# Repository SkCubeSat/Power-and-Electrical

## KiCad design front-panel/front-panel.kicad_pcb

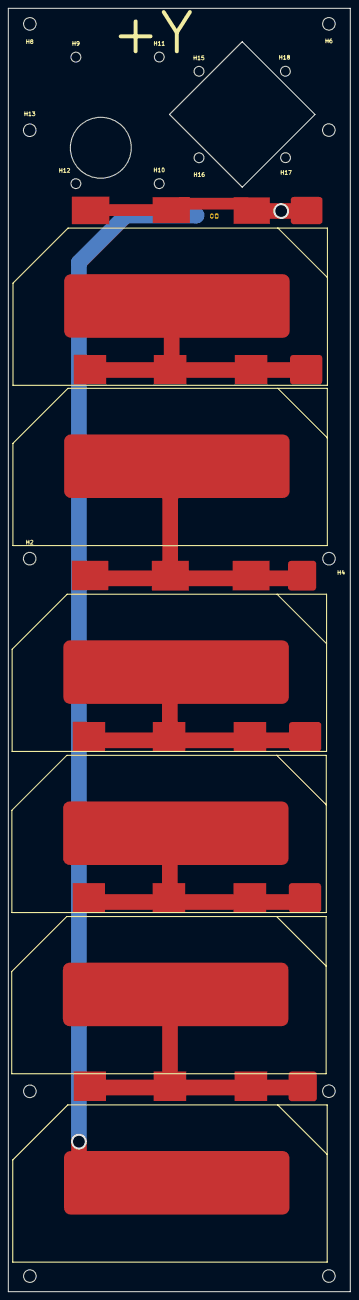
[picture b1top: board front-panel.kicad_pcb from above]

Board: 2 copper layers, 87.0 x 326.5 mm, 25 parts (1 on the bottom side), 7 nets.

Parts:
Buck2: Hirose_DF13-02P-1.25DSA_1x02_P1.25mm_Vertical
H1, H2, H3, H4, H5, H6, H7, H8, H13, H13#2: MountingHole; MountingHole_3.2mm_M3
H9, H10, H11, H12, H15, H16, H17, H18: MountingHole; MountingHole_2.5mm
SC7, SC9, SC10: S8040_CIC; Solar_Cell_Lightricity_S8040_CIC
SC8, SC11: S8040_CIC; Solar_Cell_Lightricity_S8040_CIC_Thinner_Tabs
SC14: S8040_CIC; Solar_Cell_Lightricity_S8040_CIC_Shorter_Tabs

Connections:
unnamed: Buck2.1 (BCR+), SC14.1 (+)
unnamed: Buck2.2 (BCR-), SC11.2 (-)
unnamed: SC7.2 (-), SC8.1 (+)
unnamed: SC8.2 (-), SC9.1 (+)
unnamed: SC9.2 (-), SC10.1 (+)
unnamed: SC10.2 (-), SC11.1 (+)
unnamed: SC7.1 (+), SC14.2 (-)

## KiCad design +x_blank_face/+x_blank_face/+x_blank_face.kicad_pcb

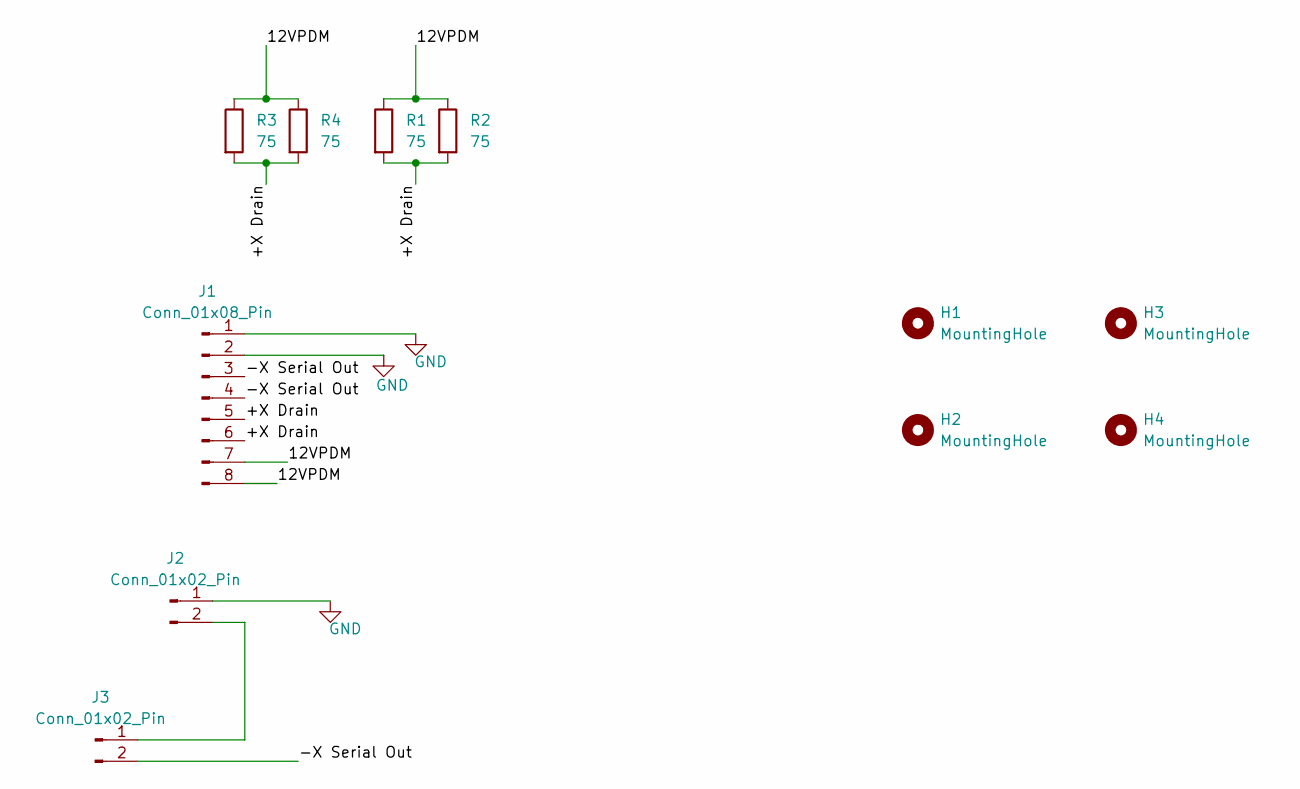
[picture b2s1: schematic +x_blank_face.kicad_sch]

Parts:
H1, H2, H3, H4: MountingHole; 2.55mm_Mounting_Hole
J1: Conn_01x08_Pin; DF13-8P
J2, J3: Conn_01x02_Pin; CON2_1X2_UR_DF13
R1, R2, R3, R4: 75; UB3C-75RF1

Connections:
/12VPDM: J1.7, J1.8, R1.1, R2.1, R3.1, R4.1
/+X Drain: J1.5, J1.6, R1.2, R2.2, R3.2, R4.2
/-X Serial Out: J1.3, J1.4, J3.2
GND: J1.1, J1.2, J2.1
unnamed: J2.2, J3.1

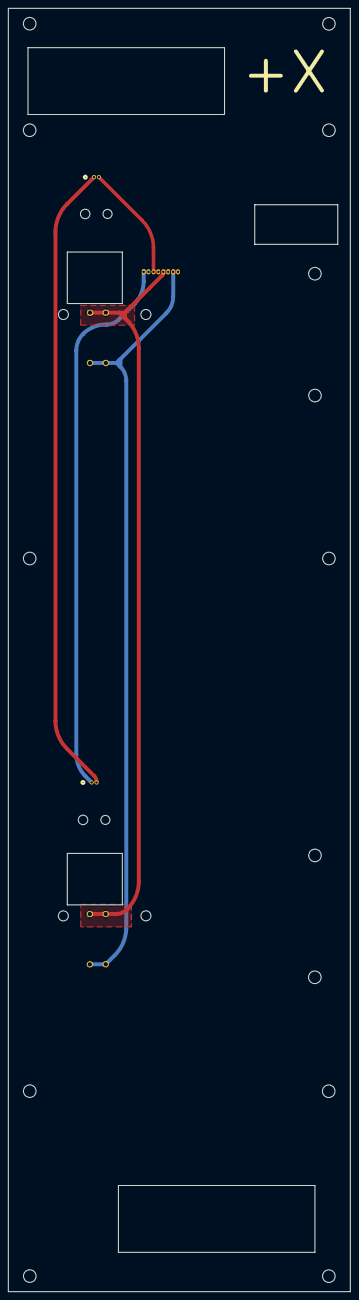
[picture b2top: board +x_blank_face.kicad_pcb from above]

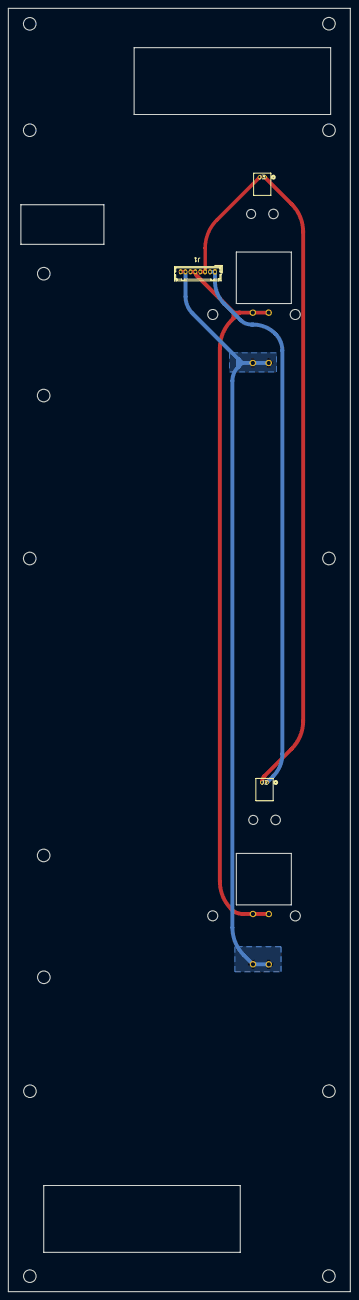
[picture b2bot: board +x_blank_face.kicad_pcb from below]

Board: 2 copper layers, 87.0 x 326.5 mm, 25 parts (3 on the bottom side), 5 nets.

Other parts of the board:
H1#2, H2#2, H4#2, H5, H6, H7, H8, H9, H10, H11, H13, H14, H15: MountingHole; MountingHole_3.2mm_M3
H3#2: MountingHole; 2.55mm_Mounting_Hole

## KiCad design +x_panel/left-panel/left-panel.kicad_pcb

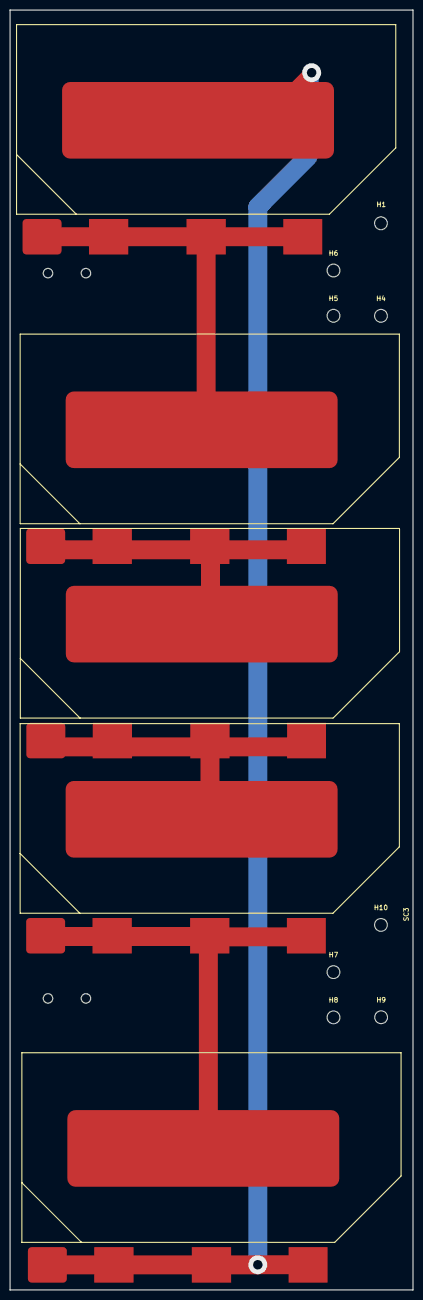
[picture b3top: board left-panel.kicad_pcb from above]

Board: 2 copper layers, 85.0 x 270.0 mm, 14 parts (1 on the bottom side), 6 nets.

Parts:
Buck1: DF13_Horizontal
H1, H4, H5, H6, H7, H8, H9, H10: MountingHole; MountingHole_2.7mm
SC1, SC3, SC4, SC5, SC6: S8040_CIC; Solar_Cell_Lightricity_S8040_CIC

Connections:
unnamed: Buck1.1 (BCR+), SC6.2 (-)
unnamed: Buck1.2 (BCR-), SC1.1 (+)
unnamed: SC1.2 (-), SC3.1 (+)
unnamed: SC3.2 (-), SC4.1 (+)
unnamed: SC4.2 (-), SC5.1 (+)
unnamed: SC5.2 (-), SC6.1 (+)

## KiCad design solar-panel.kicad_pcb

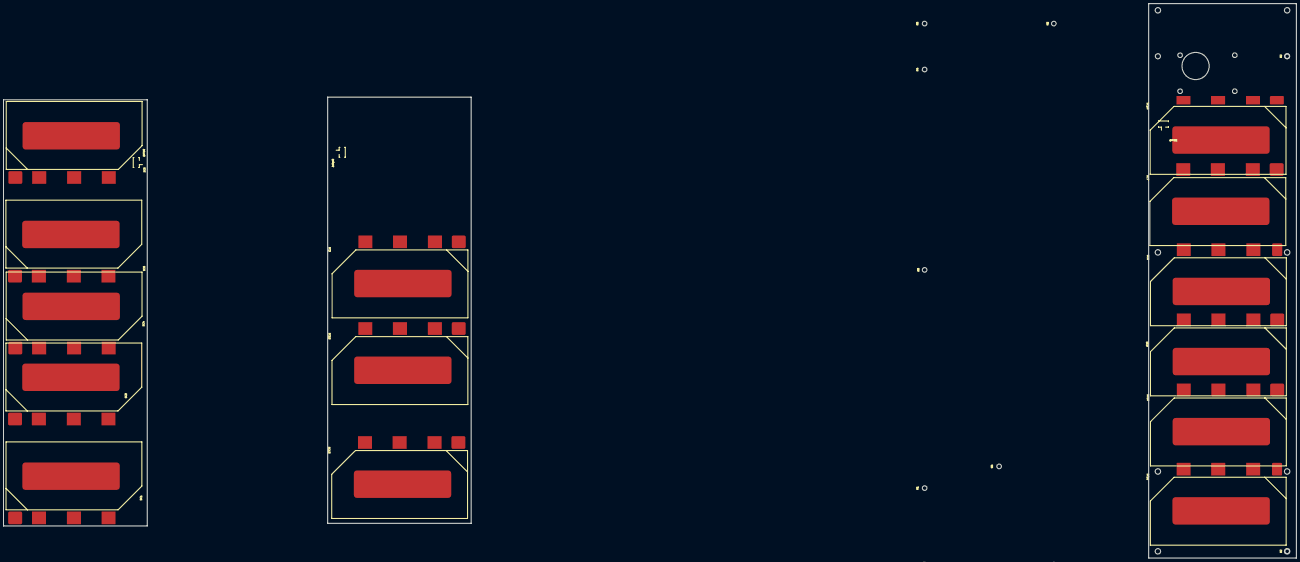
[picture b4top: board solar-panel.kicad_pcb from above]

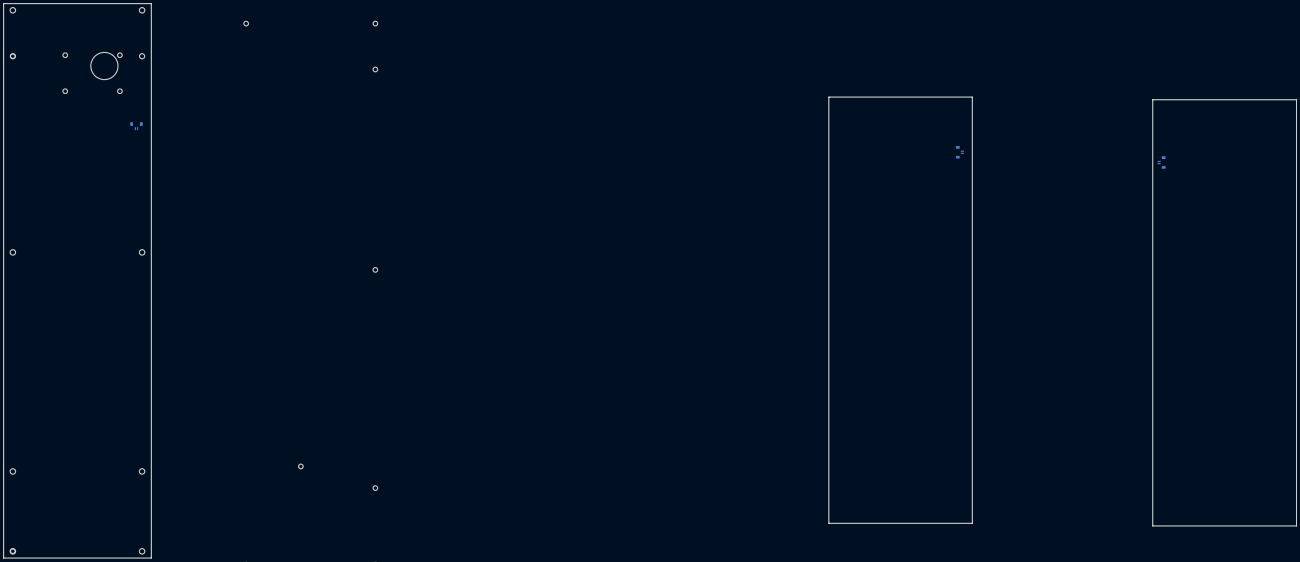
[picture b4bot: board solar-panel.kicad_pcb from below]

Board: 2 copper layers, 761.4 x 326.5 mm, 32 parts (3 on the bottom side), 17 nets, no tracks yet.

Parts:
Buck1, Buck2: 2_Hirose_Pin
H1, H1#2, H1#3, H2, H2#2, H2#3, H3, H4, H4#2, H5, H6, H7, H8, H9, H10: MountingHole; MountingHole_2.7mm
SC1, SC2, SC3, SC4, SC5, SC6, SC7, SC8, SC9, SC10, SC11, SC12, SC13, SC14: S8040_CIC; Solar_Cell_Lightricity_S8040_CIC
Sepic1: 2_Hirose_Pin

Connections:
unnamed: Buck1.1 (BCR+), SC1.1 (+)
unnamed: Buck1.2 (BCR-), SC6.2 (-)
unnamed: Buck2.1 (BCR+), SC14.1 (+)
unnamed: Buck2.2 (BCR-), SC11.2 (-)
unnamed: SC1.2 (-), SC3.1 (+)
unnamed: SC2.1 (+), Sepic1.1 (BCR+)
unnamed: SC3.2 (-), SC4.1 (+)
unnamed: SC4.2 (-), SC5.1 (+)
unnamed: SC5.2 (-), SC6.1 (+)
unnamed: SC7.2 (-), SC8.1 (+)
unnamed: SC8.2 (-), SC9.1 (+)
unnamed: SC9.2 (-), SC10.1 (+)
unnamed: SC10.2 (-), SC11.1 (+)
unnamed: SC2.2 (-), SC12.1 (+)
unnamed: SC12.2 (-), SC13.1 (+)
unnamed: SC13.2 (-), Sepic1.2 (BCR-)
unnamed: SC7.1 (+), SC14.2 (-)

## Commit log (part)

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2023-05-26 inital solar commit
2023-05-27 solar panel init
2023-05-27 added solar cell logic
2023-05-27 rev 1.0, added pdf
2023-05-28 rev 1.0 routed by Jonah
2023-05-28 added silkscreen
2023-06-26 test
2023-06-26 blank
2023-11-26 [Inhibit logic]
2023-12-03 not done yet
2023-12-03 1st change - moved mounting holes
2023-12-03 1st draft - moved mounting holes
2024-05-25 new branch
2024-06-05 created footprint for lightricity s8040_CIC cell
2024-06-08 added footprint library table added backups folder to gitignore updated project to kicad 8.0
2024-06-08 Remade schematic for all panels Fixed lightricity footprint Erased panel PCBs
2024-10-27 create input processing
2024-10-27 Fixed compilation errors Added return value reader
2024-11-03 added prints for recieved packets
2024-11-03 Changed pins for rpi pico
2024-11-03 Debuged falty code
2024-11-17 clean up old copy
2024-11-17 eliminated macro spam
2025-01-19 another rewrite of eps test script, makes it a lot more readable
2025-05-11 rearanged panels, updated solar cells footprint
2025-05-19 Added traces, added solder pads for connections (NO GND PADS)
2025-05-27 Replace solder pads with hirose df13 connections
2025-09-23 Added Mounting holes, overlapped cells, changed to 5 6 3 configuration, changed overall solar panel dimensions
2025-11-17 Updated footprint to match new knowledge of bypass diodes
2025-11-19 made projects for manufacturing each individual solar panel
2025-12-16 Added projects for blank PCBs, updated solar panels
2025-12-16 changed folder names for respective sides of panels
2026-02-22 Changes solar panels
2026-02-22 added schematic to +x and routed ish the schematic
2026-02-23 changed switch connector footprint
2026-02-27 Updated panels based on dxf drawings from mech, need to move all holes up 5mm
2026-02-27 moved holes up 5mm, did what Jack said to do
2026-02-27 Moved some things around, locked some components
2026-02-28 changed ALOT of things, got it to a point to send mech models,solar panel harness on BS need changed
2026-03-01 I forgot what I changed
2026-03-02 Rerouted some stuff
2026-03-11 removed solder mask from footprint
2026-03-11 reviewed boards
2026-04-29 Removed GND and PWR plane, replaced with traces, switches are now in series rather than in parallel
2026-04-29 Updated +X blank to remove GND and PWR plane, and changed parallel switches to series switches
2026-04-30 fixed 3d models for connectors
2026-06-16 changed cover panels to have smaller power planes, also changed front panel DF13 from SMD to THT
